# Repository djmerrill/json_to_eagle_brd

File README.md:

# JSON to EAGLE brd

Creates an EAGLE brd from a json file.

Requires NVSL/Swoop library.

`python3 builder.py --help`

### Examples 

`python3 builder.py SimpleButton.json`

`python3 builder.py VideoPlayer.json`

`python3 builder.py -i '{ "pcbHeight": 16, "pcbWidth": 56, "connector": { "schematicName": "connector_raspberrypi", "netsAvailabe": [ "4", "17", "27", "22", "5", "6", "13", "26", "18", "23", "24", "25", "12", "16", "19", "20", "21", "2", "3", "9", "10", "11", "8", "14", "15", "3.3V", "5V" ], "partsPosition": { "part_0": { "componentName": "J1", "componentX": 26.5, "componentY": 2.5 } } }, "modules": { "module_0": { "schematicName": "tactile_push_button_smd", "interfaces": { "iface_0": { "type": "gpio", "GPIO": "4" } }, "partsPosition": { "part_0": { "componentName": "S1", "componentX": 6.75, "componentY": 10 }, "part_1": { "componentName": "R1", "componentX": 15.6, "componentY": 10.8 } } } } }'`

### Debug 

`python3 builder.py --debug SimpleButton.json`

`python3 builder.py --debug -i '{ "pcbHeight": 16, "pcbWidth": 56, "connector": { "schematicName": "connector_raspberrypi", "netsAvailabe": [ "4", "17", "27", "22", "5", "6", "13", "26", "18", "23", "24", "25", "12", "16", "19", "20", "21", "2", "3", "9", "10", "11", "8", "14", "15", "3.3V", "5V" ], "partsPosition": { "part_0": { "componentName": "J1", "componentX": 26.5, "componentY": 2.5 } } }, "modules": { "module_0": { "schematicName": "tactile_push_button_smd", "interfaces": { "iface_0": { "type": "gpio", "GPIO": "4" } }, "partsPosition": { "part_0": { "componentName": "S1", "componentX": 6.75, "componentY": 10 }, "part_1": { "componentName": "R1", "componentX": 15.6, "componentY": 10.8 } } } } }'`

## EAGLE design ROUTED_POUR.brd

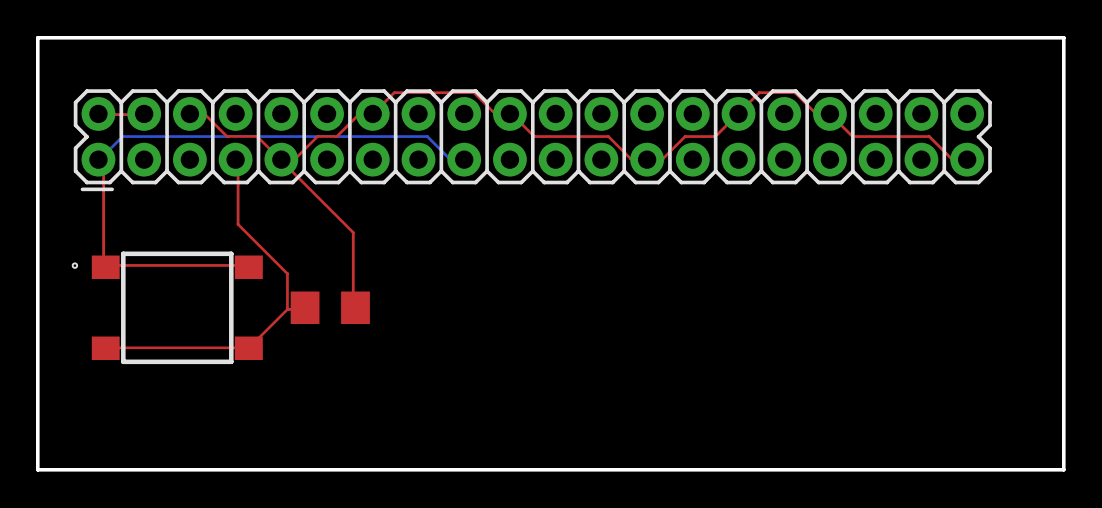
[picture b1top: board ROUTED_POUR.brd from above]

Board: 2 copper layers, 57.0 x 24.0 mm, 3 parts (0 on the bottom side), 4 nets.

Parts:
J1_CONNECTOR: CONNECTOR_RASPBERRYPI_SPARKFUN-CONNECTORS_RASPBER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; CONNECTOR_RASPBERRYPI_SPARKFUN-CONNECTORS_2X20
R1_MODULE_0: 1206
S1_MODULE_0: PTS645SL50SMTR92LFS_PTS645SL50SMTR92LFS; PTS645SL50SMTR92LFS_PTS645SMT

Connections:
3.3V: J1_CONNECTOR.1, J1_CONNECTOR.17, S1_MODULE_0.1, S1_MODULE_0.2
4: J1_CONNECTOR.7, R1_MODULE_0.1, S1_MODULE_0.3, S1_MODULE_0.4
5V: J1_CONNECTOR.2, J1_CONNECTOR.4
GND: J1_CONNECTOR.6, J1_CONNECTOR.9, J1_CONNECTOR.14, J1_CONNECTOR.20, J1_CONNECTOR.25, J1_CONNECTOR.30, J1_CONNECTOR.34, J1_CONNECTOR.39, R1_MODULE_0.2

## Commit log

2020-02-14 initial
2020-02-18 added board template
2020-02-19 Fix connector poss, Added -i option for json input as arg, added pyPath to get folder path
2020-03-18 Fix smd push button and examples
2020-04-08 Adding board boarders and required CAM files
2020-04-08 Adding Gerber dir
2020-04-08 Adding Emtpty Gerber dir
2020-04-08 Remove vscode dir
2020-04-10 Adding SimpleLed test sample
2020-04-13 Adding cooper pouring
2020-04-14 Fix find_device() error
2020-04-21 Fix paths
2020-05-30 Fix board modules
2020-06-12 Add cooper pour separately
2020-06-12 clean git
